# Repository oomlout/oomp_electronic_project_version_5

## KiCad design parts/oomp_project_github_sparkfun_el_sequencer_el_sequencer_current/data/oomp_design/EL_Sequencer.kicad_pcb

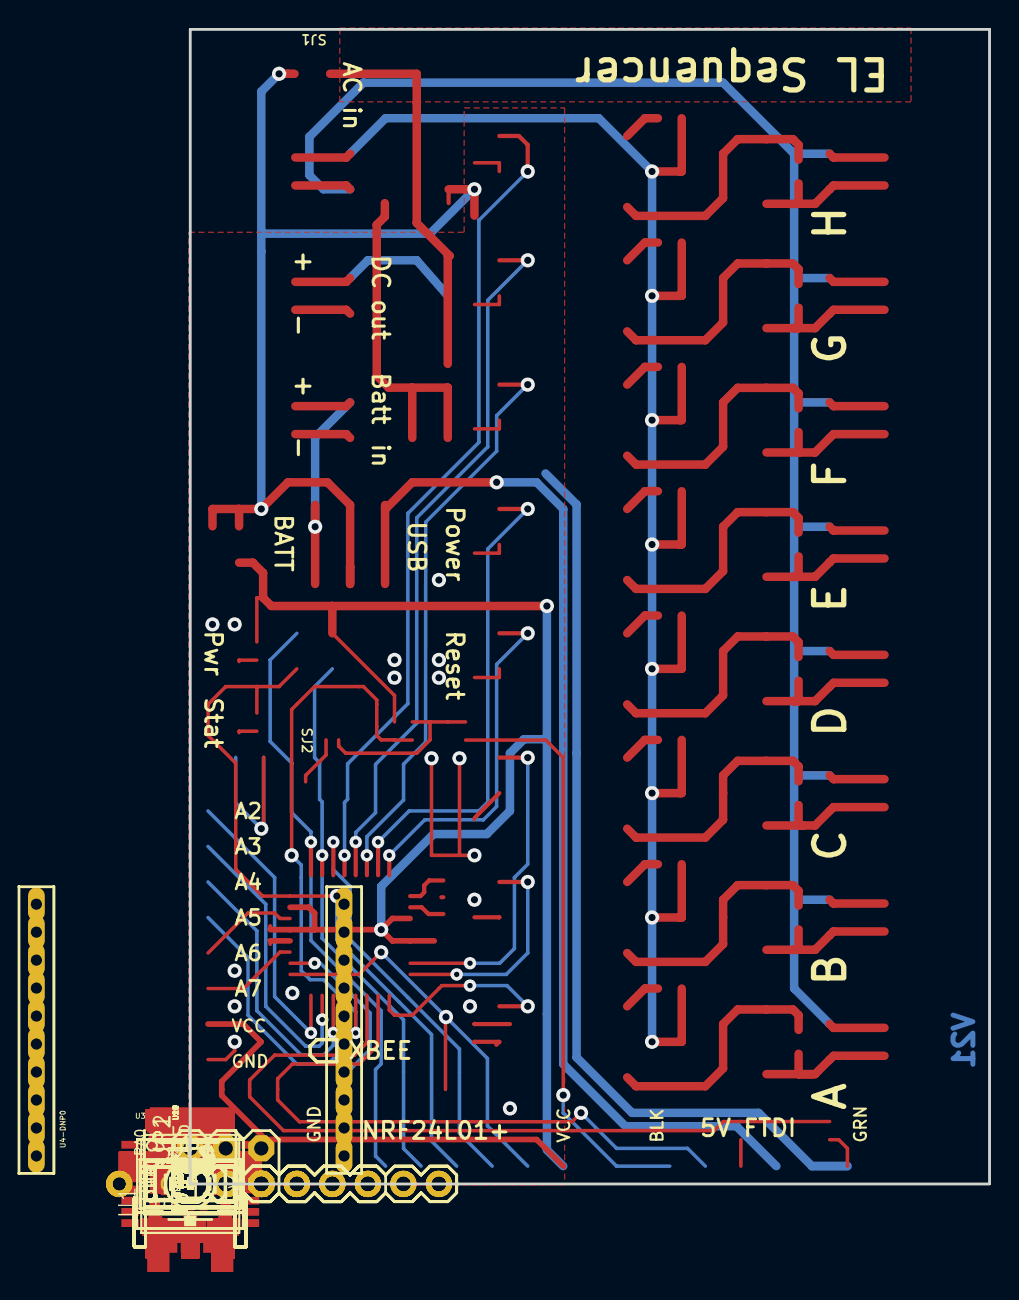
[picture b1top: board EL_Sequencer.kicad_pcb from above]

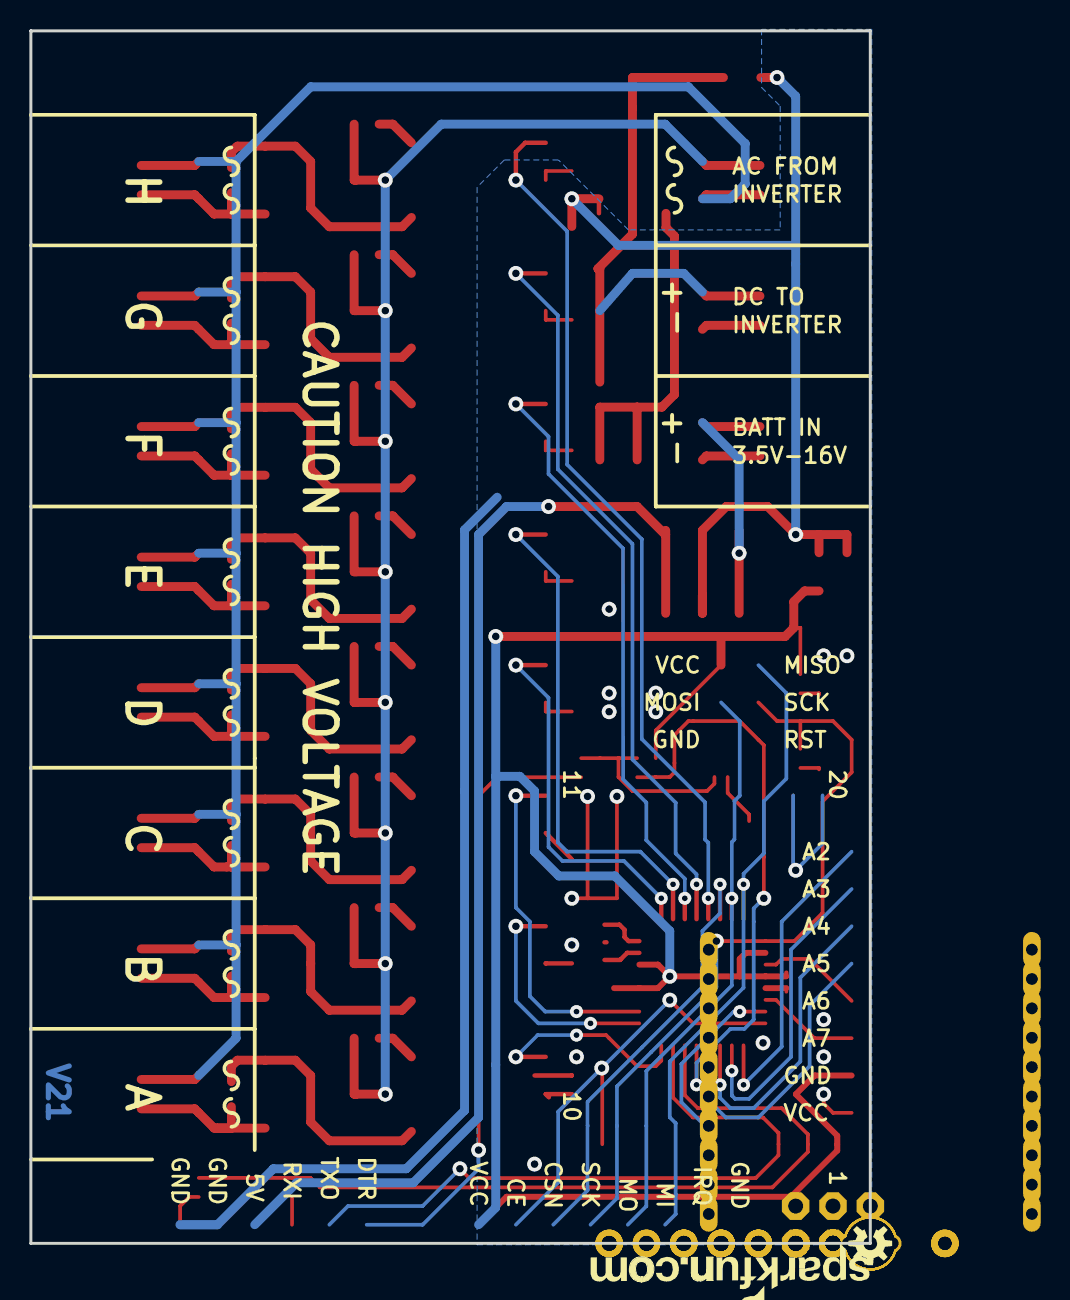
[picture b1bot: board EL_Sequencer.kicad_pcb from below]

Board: 2 copper layers, 57.1 x 82.5 mm, 106 parts (2 on the bottom side), 72 nets.

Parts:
C1, C4, C5, C6, C7: 0.1uF; 0402-CAP
C2, C3: 10uF; EIA3216
FRAME1, FRAME2: FRAME-LETTER; CREATIVE_COMMONS
J1: Battery; JST-2-SMD
J2: DC-OUTPUT; JST-2-SMD
J3: AC-INPUT; JST-2-SMD
J4, J5, J6, J7, J8, J9, J10, J11: JST-2-SMD
JP1, JP6, JP7, JP9, JP10, JP11, JP12, JP13, JP14, JP15, JP16: 1X02
JP2: I/O; 1X08_ROUND
JP3: 5V_FTDI; 1X06
JP4: nRF24L01; 1X08
JP5: PROG; 2X3
JP8: LOGO-SFESK; SFE-LOGO-FLAME
LED1: Power; LED-0603
LED2: Status; LED-0603
R1: 390; 0603-RES
R2: 240; 0603-RES
R3, R5, R7, R9: 1K; 0402-RES
R4, R6: 2K; 0402-RES
R8: 10K; 0402-RES
R10, R11, R12, R13, R22, R23, R24, R25: 390; 0402-RES
R14, R15, R16, R17, R18, R19, R20, R21, R26, R27, R28, R29, R30, R31, R32, R33: 330; 0603-RES
RA0: A; AXIAL-0.4
RB0: B; AXIAL-0.4
S1: POWER; AYZ0202
S2: RESET; TACTILE_SWITCH_SMD
SJ1: SJ_ROUND
SJ2: SJ_2S-NO
U1: LM317; V-REG_DPACK
U2: MIC5219-3.3; SOT23-5
U3: ATMEGA328P; TQFP32-08
U4-DNP0: XBEE HEADER; XBEE-LONGPAD
U5, U6, U7, U8, U13, U14, U15, U16: MOC3063S; DIP8SMD
U9, U10, U11, U12, U17, U18, U19, U20: Z0103MN; SOT223
U$1: OSHW-LOGOS; OSHW-LOGO-S
U$2: LOGO-SFENEW; SFE-NEW-WEBLOGO
U$3, U$4: FIDUCIALUFIDUCIAL; MICRO-FIDUCIAL
U$5, U$6, U$7, U$8: STAND-OFF
Y1: 8MHz; RESONATOR-SMD

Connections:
5VUSB: JP3.4, S1.3, S1.6
ADC_2: JP2.8, U3.25
ADC_3: JP2.7, U3.26
ADC_4: JP2.6, U3.27
ADC_5: JP2.5, U3.28
ADC_6*: JP2.4, U3.19
ADC_7*: JP2.3, U3.22
CE/SLEEP: JP4.7, U3.24, U4-DNP0.9
CSN: JP4.6, U3.14
DTR: C5.1, R5.1, R6.2, SJ2.2
EL_A: U3.32, U5.1
EL_B: U3.1, U6.1
EL_C: U3.2, U7.1
EL_D: U3.9, U8.1
EL_E: U3.10, U13.1
EL_F: U3.11, U14.1
EL_G: U3.12, U15.1
EL_H: U3.13, U16.1
FTDI_DTR: JP3.1, R5.2
FTDI_RXI: JP3.3, R3.2
GND: C1.2, C2.C, C3.C, C4.2, C6.2, C7.2, J1.1, J2.1, JP1.1, JP2.1, JP3.5, JP3.6, JP4.1, JP5.6, JP6.2, LED1.C, LED2.C, R1.1, R4.1, R6.1, R10.1, R11.1, R12.1, R13.1, R22.1, R23.1, R24.1, R25.1, RB0.P$1, S2.3, U2.2, U3.3, U3.5, U3.21, U4-DNP0.10, Y1.2
HV: J3.2, JP7.1, R14.2, R16.2, R18.2, R20.2, R26.2, R28.2, R30.2, R32.2, U9.4, U10.4, U11.4, U12.4, U17.4, U18.4, U19.4, U20.4
HVGND: J3.1, J4.1, J5.1, J6.1, J7.1, J8.1, J9.1, J10.1, J11.1, JP7.2, JP9.1, JP10.1, JP11.1, JP12.1, JP13.1, JP14.1, JP15.1, JP16.1
INV: C2.A, J2.2, JP6.1, R2.2, RA0.P$2, SJ1.2, U1.4
IRQ: JP4.2, U3.23
MISO: JP4.3, JP5.1, U3.16
MOSI: JP4.4, JP5.4, U3.15
unnamed: U3.7, Y1.1
unnamed: R17.1, U6.4, U10.3
unnamed: R11.2, U6.2
unnamed: LED1.A, R7.1
unnamed: R16.1, U6.6
unnamed: U3.8, Y1.3
unnamed: R10.2, U5.2
unnamed: SJ2.1, U4-DNP0.17
unnamed: J5.2, JP10.2, R17.2, U10.1
unnamed: R19.1, U7.4, U11.3
unnamed: R14.1, U5.6
unnamed: R12.2, U7.2
unnamed: R1.2, R2.1, RA0.P$1, RB0.P$2, U1.1
unnamed: LED2.A, R9.1
unnamed: R18.1, U7.6
unnamed: J6.2, JP11.2, R19.2, U11.1
unnamed: R21.1, U8.4, U12.3
unnamed: R13.2, U8.2
unnamed: R20.1, U8.6
unnamed: J7.2, JP12.2, R21.2, U12.1
unnamed: J4.2, JP9.2, R15.2, U9.1
unnamed: R27.1, U13.4, U17.3
unnamed: R22.2, U13.2
unnamed: R26.1, U13.6
unnamed: J8.2, JP13.2, R27.2, U17.1
unnamed: R29.1, U14.4, U18.3
unnamed: R23.2, U14.2
unnamed: R28.1, U14.6
unnamed: J9.2, JP14.2, R29.2, U18.1
unnamed: R31.1, U15.4, U19.3
unnamed: R24.2, U15.2
unnamed: R30.1, U15.6
unnamed: J10.2, JP15.2, R31.2, U19.1
unnamed: R33.1, U16.4, U20.3
unnamed: R25.2, U16.2
unnamed: R32.1, U16.6
unnamed: J11.2, JP16.2, R33.2, U20.1
unnamed: R15.1, U5.4, U9.3
RAW: C1.1, S1.2, S1.5, SJ1.1, U1.3, U2.1, U2.3
RST: C5.2, JP5.5, R8.1, S2.1, U3.29
RXI: R3.1, R4.2, U3.30, U4-DNP0.2
SCK: JP4.5, JP5.3, R9.2, U3.17
TXO: JP3.2, U3.31, U4-DNP0.3
VBATT: J1.2, JP1.2, S1.1, S1.4
VCC: C3.A, C4.1, C6.1, C7.1, JP2.2, JP4.8, JP5.2, R7.2, R8.2, U2.5, U3.4, U3.6, U3.18, U3.20, U4-DNP0.1

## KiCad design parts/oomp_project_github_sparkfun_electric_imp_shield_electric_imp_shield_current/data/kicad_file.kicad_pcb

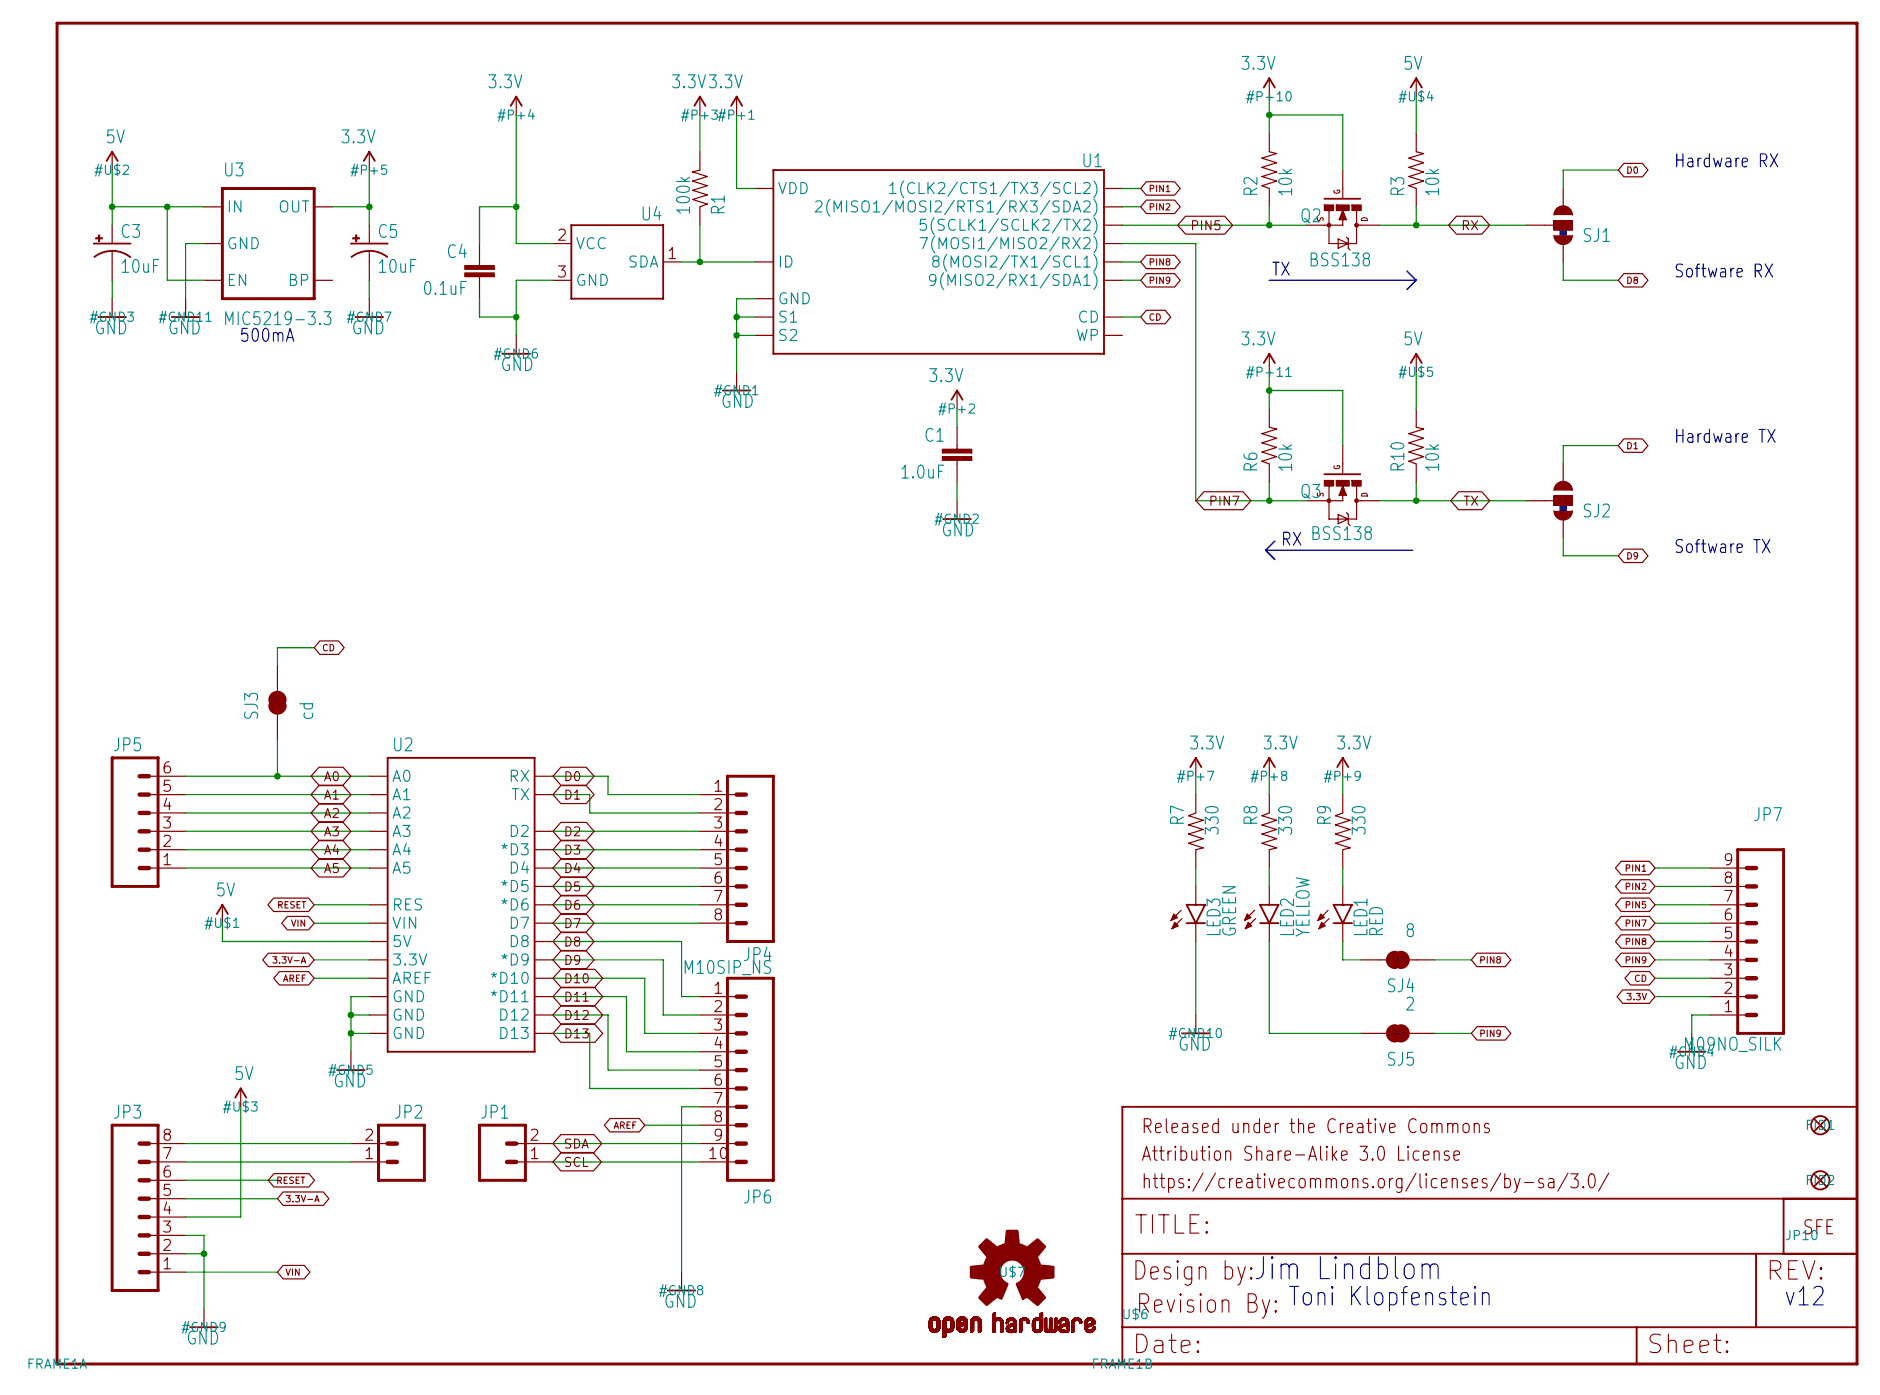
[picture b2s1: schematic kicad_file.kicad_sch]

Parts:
C1: 1.0uF; 0603-CAP
C3, C5: 10uF; EIA3216
C4: 0.1uF; 0603-CAP
FID1, FID2: FIDUCIAL1X2; FIDUCIAL-1X2
FRAME1: FRAME-LETTER; CREATIVE_COMMONS
JP1, JP2: M021X02_NO_SILK; 1X02_NO_SILK
JP3, JP4: M08SIP_NS; 1X08_NO_SILK
JP5: M06SIP_NS; 1X06_NO_SILK
JP6: M10SIP_NS; 1X10_NO_SILK
JP7: M09NO_SILK; 1X09_NO_SILK
JP10: LOGO-SFENW2; SFE-NEW-WEB
LED1: RED; LED-0603
LED2: YELLOW; LED-0603
LED3: GREEN; LED-0603
Q2, Q3: BSS138; SOT23-3
R1: 100k; 0603-RES
R2, R3, R6, R10: 10k; 0603-RES
R7, R8, R9: 330; 0603-RES
SJ1, SJ2: SOLDERJUMPER_2WAYS; SJ_3
SJ3: cd; SJ_2S-TRACE
SJ4: 8; SJ_2S-TRACE
SJ5: 2; SJ_2S-TRACE
U1: ELECTRIC_IMP; SD_1_1
U2: ARDUINO_SHIELD; DUEMILANOVE_SHIELD_NOHOLES_NOLABELS
U3: MIC5219-3.3; SOT23-5
U4: ATSHA204-TSU; SOT23-3
U$6: REVISION
U$7: OSHW-LOGOS; OSHW-LOGO-S

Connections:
3.3V: C1.1, C4.1, C5.A (+), JP7.2, Q2.1 (G), Q3.1 (G), R1.2, R2.2, R6.2, R7.1, R8.1, R9.1, U1.4 (VDD), U3.5 (OUT), U4.2 (VCC)
3.3V-A: JP3.5, U2.3.3V
5V: C3.A (+), JP3.4, R3.2, R10.2, U2.5V, U3.1 (IN), U3.3 (EN)
A0: JP5.6, SJ3.1, U2.A0
A1: JP5.5, U2.A1
A2: JP5.4, U2.A2
A3: JP5.3, U2.A3
A4: JP5.2, U2.A4
A5: JP5.1, U2.A5
ACTIVITY: LED1.C, SJ4.2
AREF: JP6.8, U2.AREF
CD: JP7.3, SJ3.2, U1.CD
D0: JP4.1, SJ1.3, U2.RX
D1: JP4.2, SJ2.3, U2.TX
D2: JP4.3, U2.D2
D3: JP4.4, U2.D3 (*D3)
D4: JP4.5, U2.D4
D5: JP4.6, U2.D5 (*D5)
D6: JP4.7, U2.D6 (*D6)
D7: JP4.8, U2.D7
D8: JP6.1, SJ1.1, U2.D8
D9: JP6.2, SJ2.1, U2.D9 (*D9)
D10: JP6.3, U2.D10 (*D10)
D11: JP6.4, U2.D11 (*D11)
D12: JP6.5, U2.D12
D13: JP6.6, U2.D13
GND: C1.2, C3.C (-), C4.2, C5.C (-), JP3.2, JP3.3, JP6.7, JP7.1, LED3.C, U1.3 (GND), U1.SH@1 (S1), U1.SH@2 (S2), U2.GND@0 (GND), U2.GND@1 (GND), U2.GND@2 (GND), U3.2 (GND), U4.3 (GND)
LINK: LED2.C, SJ5.2
unnamed: R1.1, U1.6 (ID), U4.1 (SDA)
unnamed: JP2.2, JP3.8
unnamed: JP2.1, JP3.7
unnamed: LED3.A, R7.2
unnamed: LED2.A, R8.2
unnamed: LED1.A, R9.2
PIN1: JP7.9, U1.1 (1(CLK2/CTS1/TX3/SCL2))
PIN2: JP7.8, U1.2 (2(MISO1/MOSI2/RTS1/RX3/SDA2))
PIN5: JP7.7, Q2.2 (S), R2.1, U1.5 (5(SCLK1/SCLK2/TX2))
PIN7: JP7.6, Q3.2 (S), R6.1, U1.7 (7(MOSI1/MISO2/RX2))
PIN8: JP7.5, SJ4.1, U1.8 (8(MOSI2/TX1/SCL1))
PIN9: JP7.4, SJ5.1, U1.9 (9(MISO2/RX1/SDA1))
RESET: JP3.6, U2.RES
RX: Q2.3 (D), R3.1, SJ1.2
SCL: JP1.1, JP6.10
SDA: JP1.2, JP6.9
TX: Q3.3 (D), R10.1, SJ2.2
VIN: JP3.1, U2.VIN

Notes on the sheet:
v12
Jim Lindblom
Software TX
Hardware RX
Software RX
Hardware TX
Toni Klopfenstein
500mA

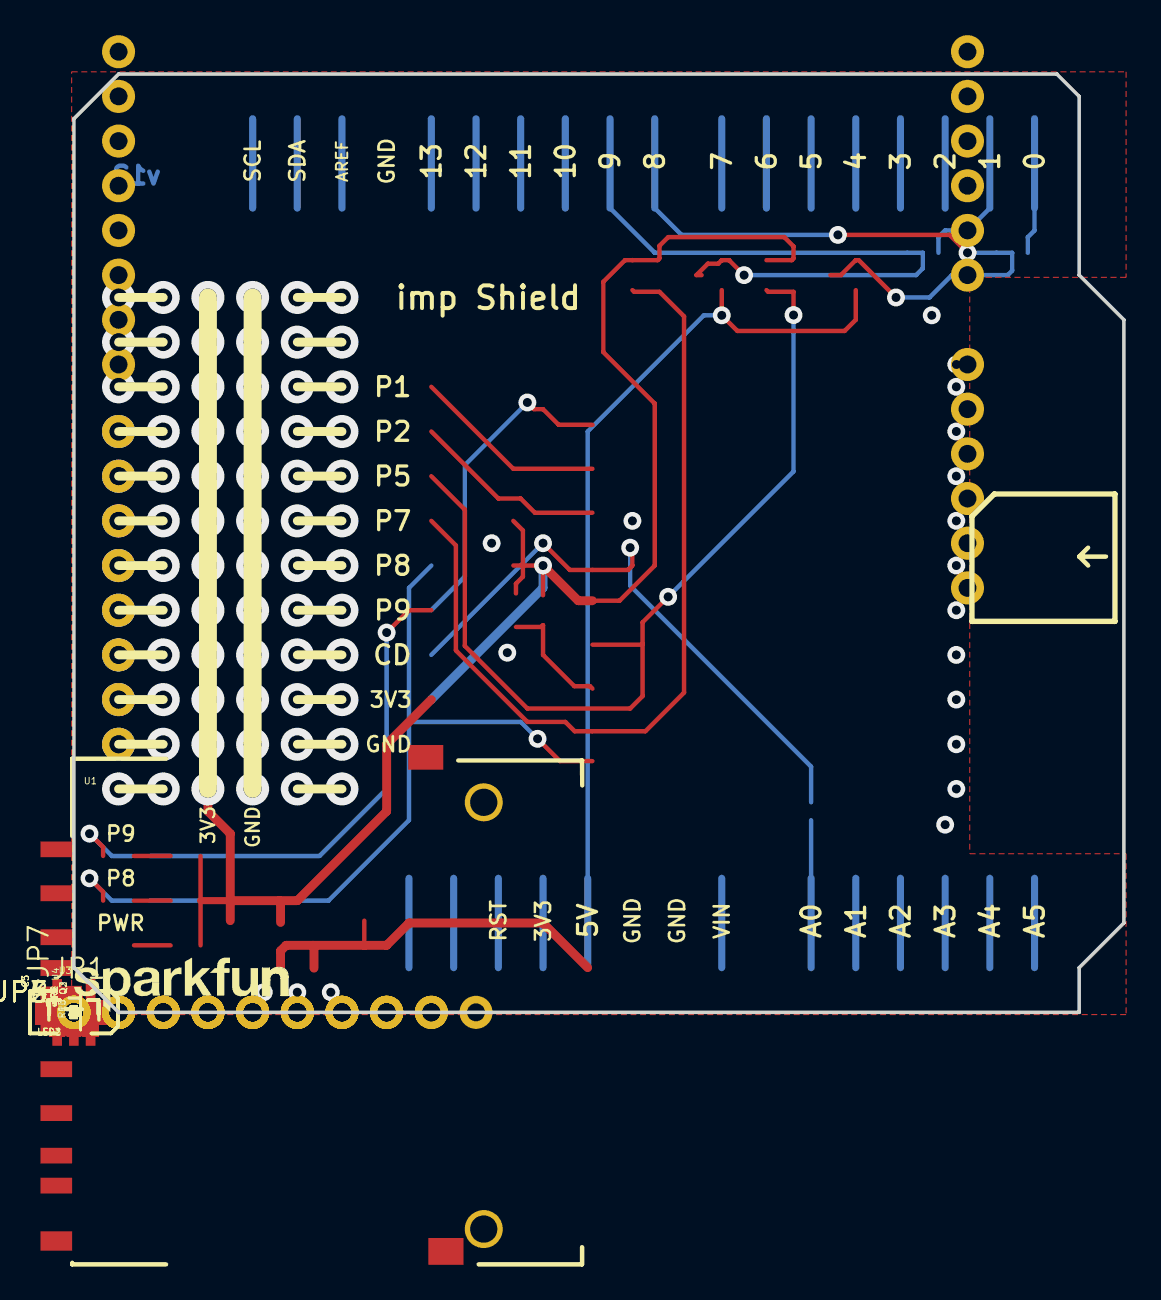
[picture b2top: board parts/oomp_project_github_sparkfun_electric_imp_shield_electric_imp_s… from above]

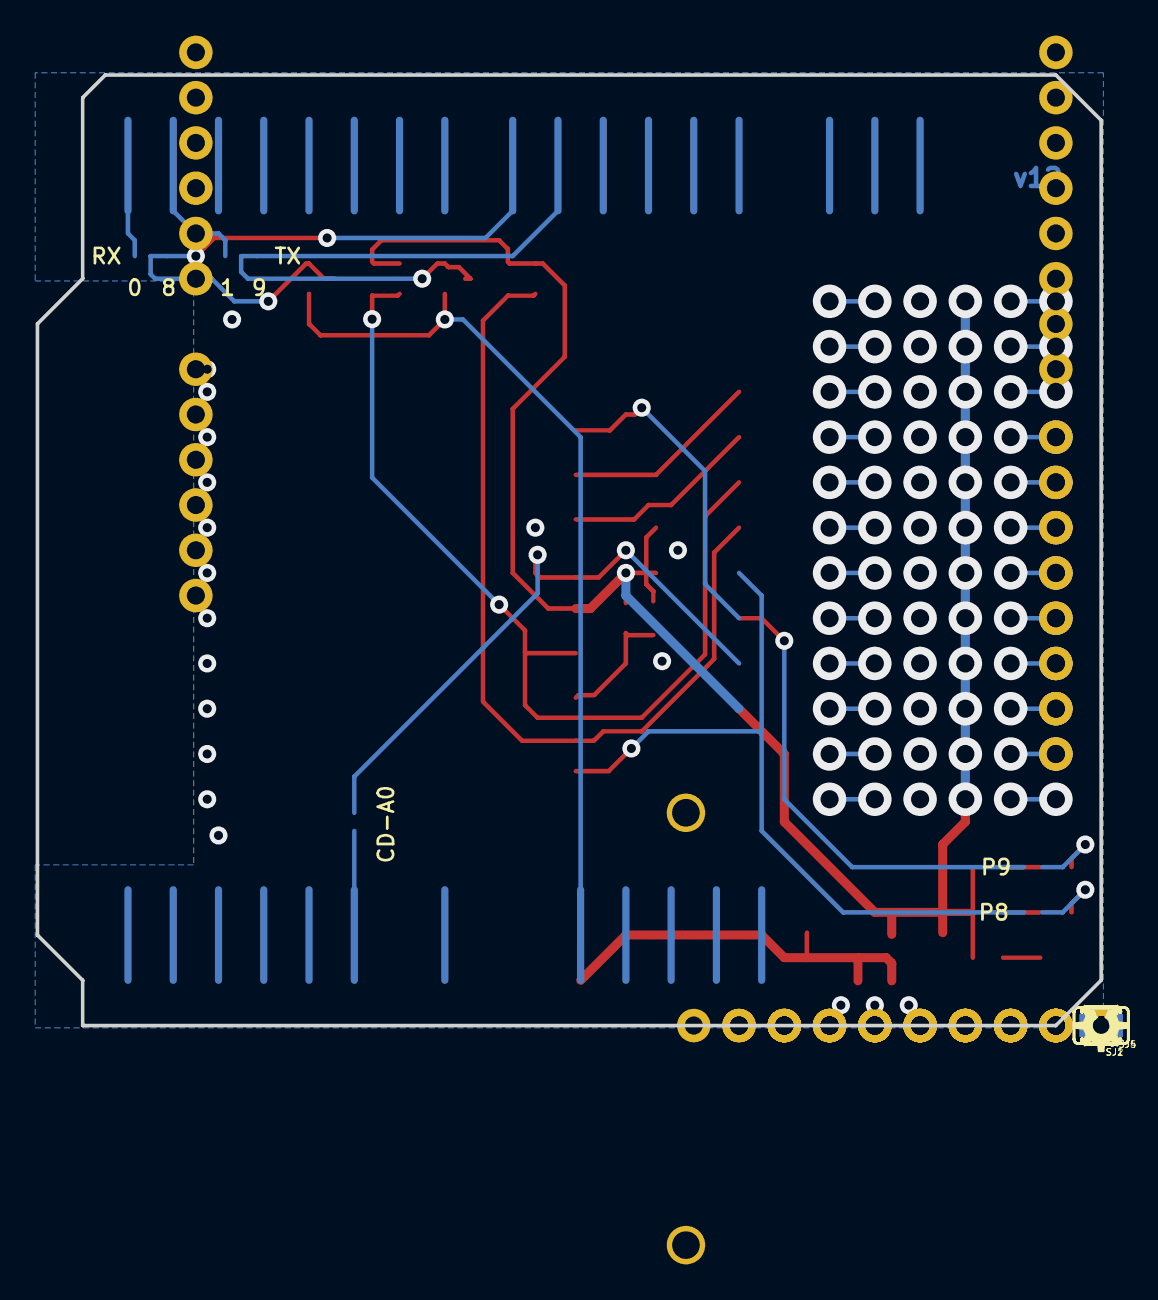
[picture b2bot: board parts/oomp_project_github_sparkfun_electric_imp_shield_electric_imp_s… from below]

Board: 2 copper layers, 59.7 x 53.3 mm, 39 parts (6 on the bottom side), 46 nets.

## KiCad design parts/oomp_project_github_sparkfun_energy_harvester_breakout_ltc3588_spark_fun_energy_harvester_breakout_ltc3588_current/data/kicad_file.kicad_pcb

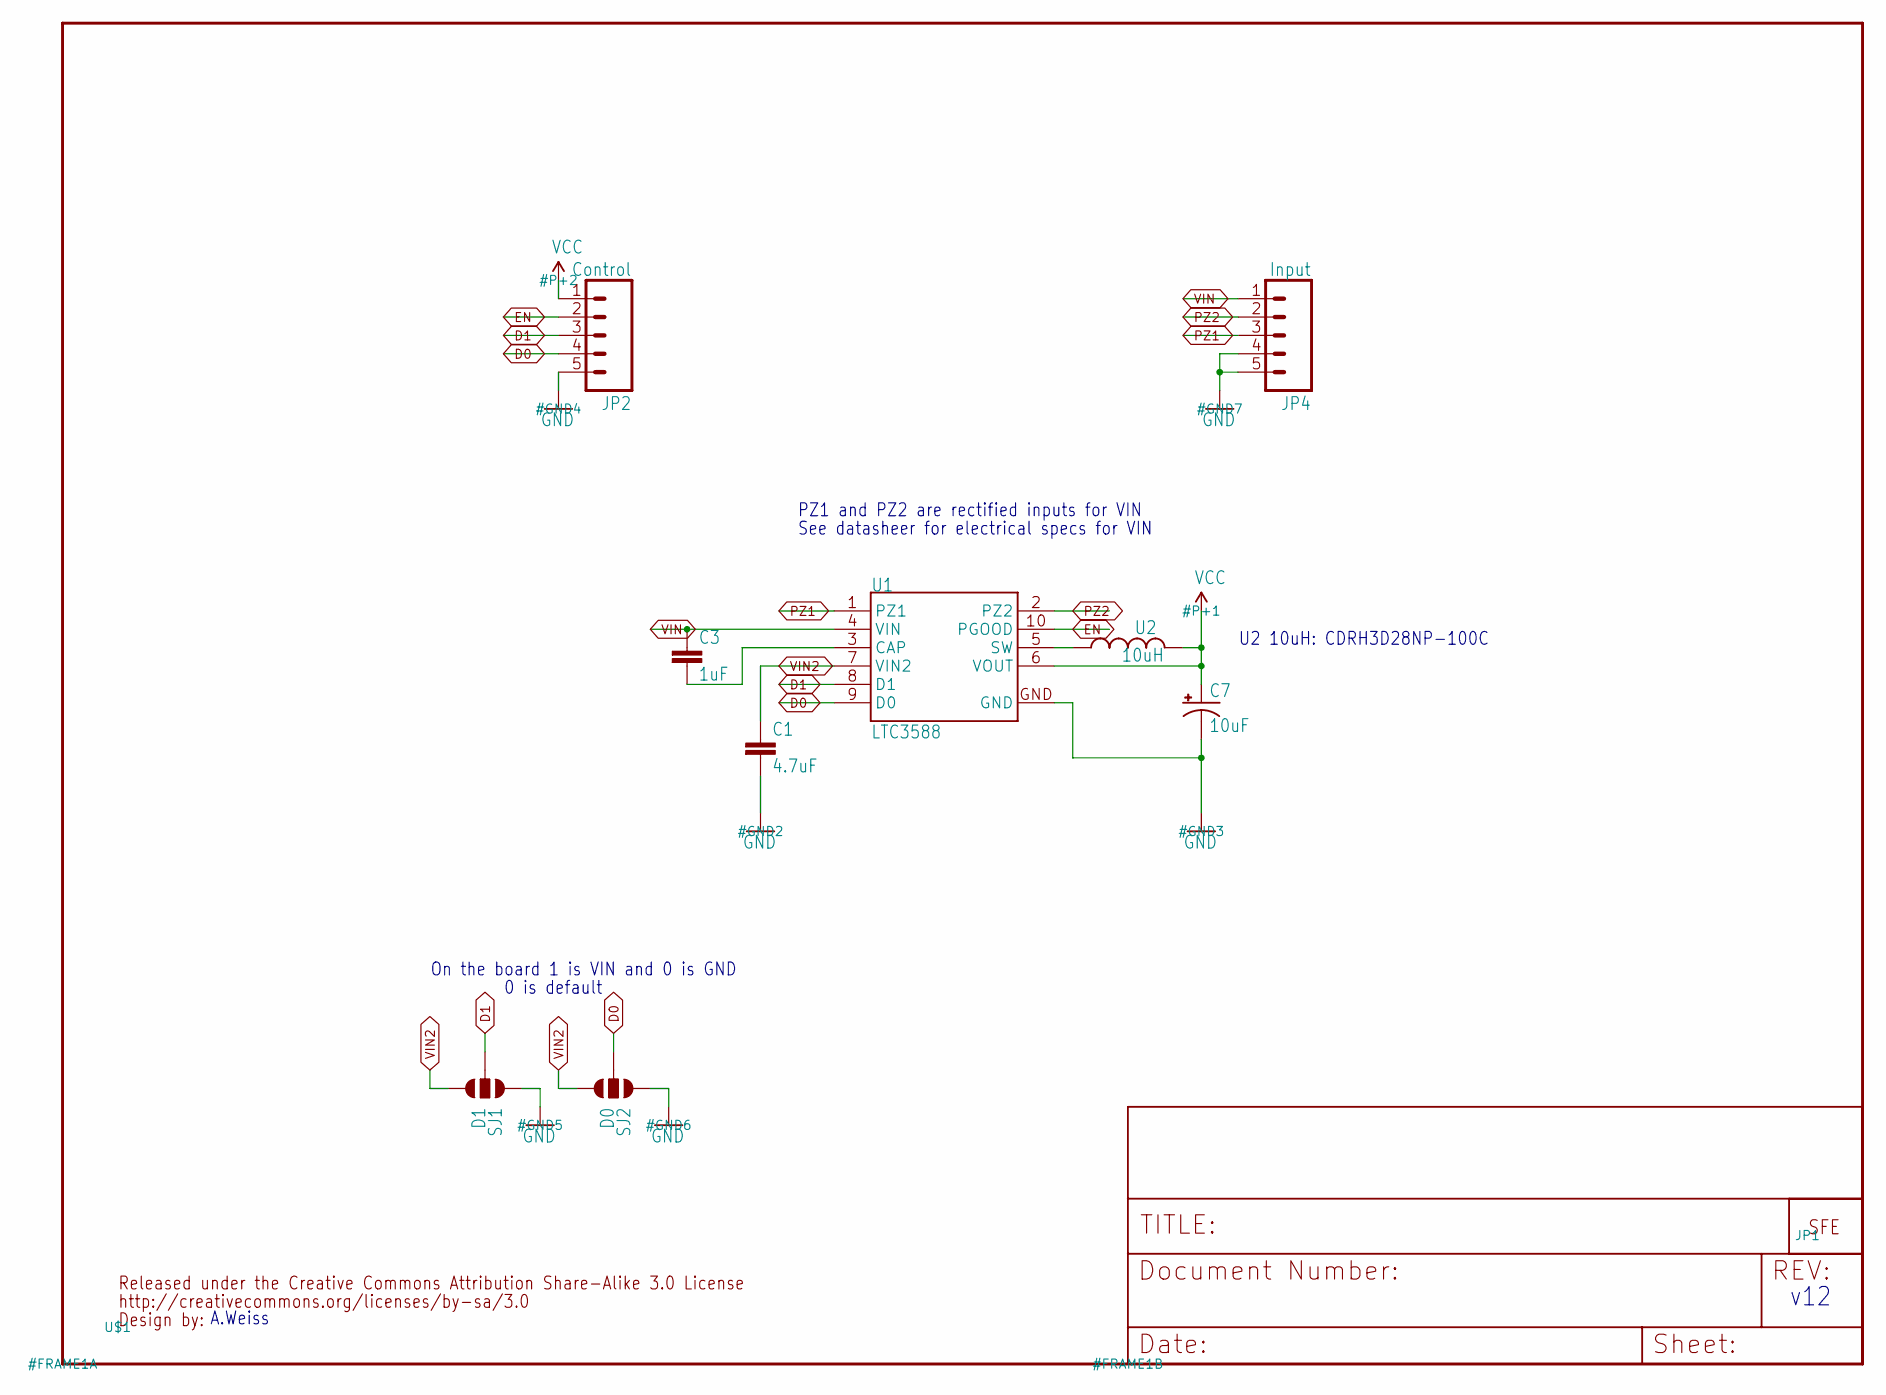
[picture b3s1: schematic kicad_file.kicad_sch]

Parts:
C1: 4.7uF; 0402-CAP
C3: 1uF; 0402-CAP
C7: 10uF; EIA3216
JP1: LOGO-SFESK; SFE-LOGO-FLAME
JP2: Control; 1X05
JP4: Input; 1X05
SJ1: D1; SJ_3_PASTE2&3
SJ2: D0; SJ_3_PASTE1&2
U1: LTC3588; MSOP-10-GNDPAD
U2: 10uH; CDRH3D28
U$1: CREATIVE_COMMONS

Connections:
D0: JP2.4, SJ2.2, U1.9 (D0)
D1: JP2.3, SJ1.2, U1.8 (D1)
EN: JP2.2, U1.10 (PGOOD)
GND: C1.2, C7.C (-), JP2.5, JP4.4, JP4.5, SJ1.1, SJ2.1, U1.GND
unnamed: C3.2, U1.3 (CAP)
unnamed: U1.5 (SW), U2.1
PZ1: JP4.3, U1.1 (PZ1)
PZ2: JP4.2, U1.2 (PZ2)
VCC: C7.A (+), JP2.1, U1.6 (VOUT), U2.2
VIN: C3.1, JP4.1, U1.4 (VIN)
VIN2: C1.1, SJ1.3, SJ2.3, U1.7 (VIN2)

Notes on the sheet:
A.Weiss
0 is default
See datasheer for electrical specs for VIN
PZ1 and PZ2 are rectified inputs for VIN
v12
On the board 1 is VIN and 0 is GND
U2 10uH: CDRH3D28NP-100C

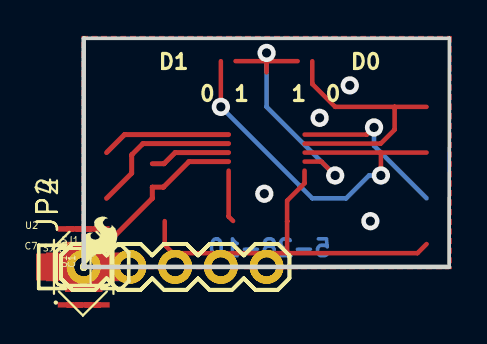
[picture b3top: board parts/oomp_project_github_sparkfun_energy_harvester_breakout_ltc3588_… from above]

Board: 2 copper layers, 20.3 x 12.7 mm, 11 parts (0 on the bottom side), 11 nets.

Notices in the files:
parts/oomp_project_github_sparkfun_el_sequencer_el_sequencer_current/data/original/kicad_file.kicad_sch:
Released under the Creative Commons
http://creativecommons.org/licenses/by-sa/3.0
parts/oomp_project_github_sparkfun_electric_imp_shield_electric_imp_shield_current/data/kicad_file.kicad_sch:
https://creativecommons.org/licenses/by-sa/3.0
parts/oomp_project_github_sparkfun_energy_harvester_breakout_ltc3588_spark_fun_energy_harvester_breakout_ltc3588_current/data/original/kicad_file.kicad_sch:
Released under the Creative Commons Attribution Share-Alike 3.0 License
